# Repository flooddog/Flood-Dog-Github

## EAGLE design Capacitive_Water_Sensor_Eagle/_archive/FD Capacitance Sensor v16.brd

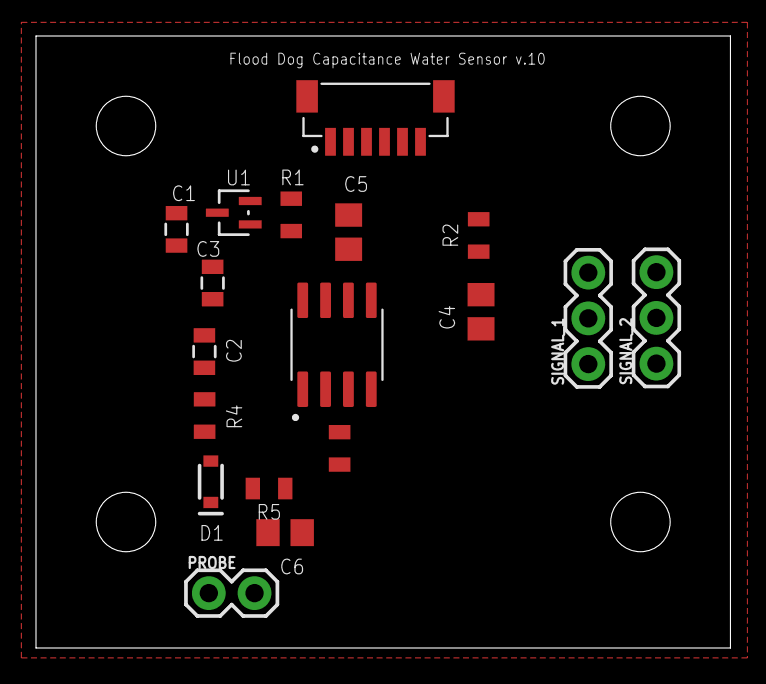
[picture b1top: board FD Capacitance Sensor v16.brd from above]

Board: 2 copper layers, 38.6 x 34.0 mm, 22 parts (0 on the bottom side), 12 nets, no tracks yet.

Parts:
C1: 0.1uF; 0805@1
C2: 1uF; 0805@1
C3: 10nF; 0805@1
C4: 10nf; C0805
C5: 470pf; C0805
C6: 1uF; C0805
D1: 250mA/100V; SOD-323
J1: BM06B-SRSS-TBT(LF)(SN); JST_BM06B-SRSS-TB(LF)(SN)
PROBE: 1X02
R1: 100k; 0805
R2: 1k; 0805
R3: 10k; 0805
R4: 330; 0805
R5: 1M; 0805
SIGNAL_1, SIGNAL_2: 1X03
U1: NTS4101PT1; SOT_101PT1_ONS
U2: TLC555CD; SOIC127P599X175-8N
U$1, U$2, U$3, U$4: STAND-OFF

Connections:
!EN: J1.3, R1.1, U1.1
+3V3: J1.2, R1.2, U1.2
GND: C1.2, C2.2, C3.2, C4.1, C5.1, C6.1, J1.1, J1.S1, J1.S2, PROBE.2, R5.1, SIGNAL_1.1, SIGNAL_2.1, U2.1
unnamed: C4.2, U2.5
unnamed: R3.1, U2.3
unnamed: C5.2, R2.1, U2.2, U2.6
unnamed: R2.2, R4.1, U2.7
PROBE+: D1.A, PROBE.1, R3.2
SIGNAL_A0: C6.2, D1.C, J1.4, R5.2
SIGNAL_A1: J1.5, SIGNAL_1.3
SIGNAL_A2: J1.6, SIGNAL_2.3
VCC: C1.1, C2.1, C3.1, R4.2, SIGNAL_1.2, SIGNAL_2.2, U1.3, U2.4, U2.8

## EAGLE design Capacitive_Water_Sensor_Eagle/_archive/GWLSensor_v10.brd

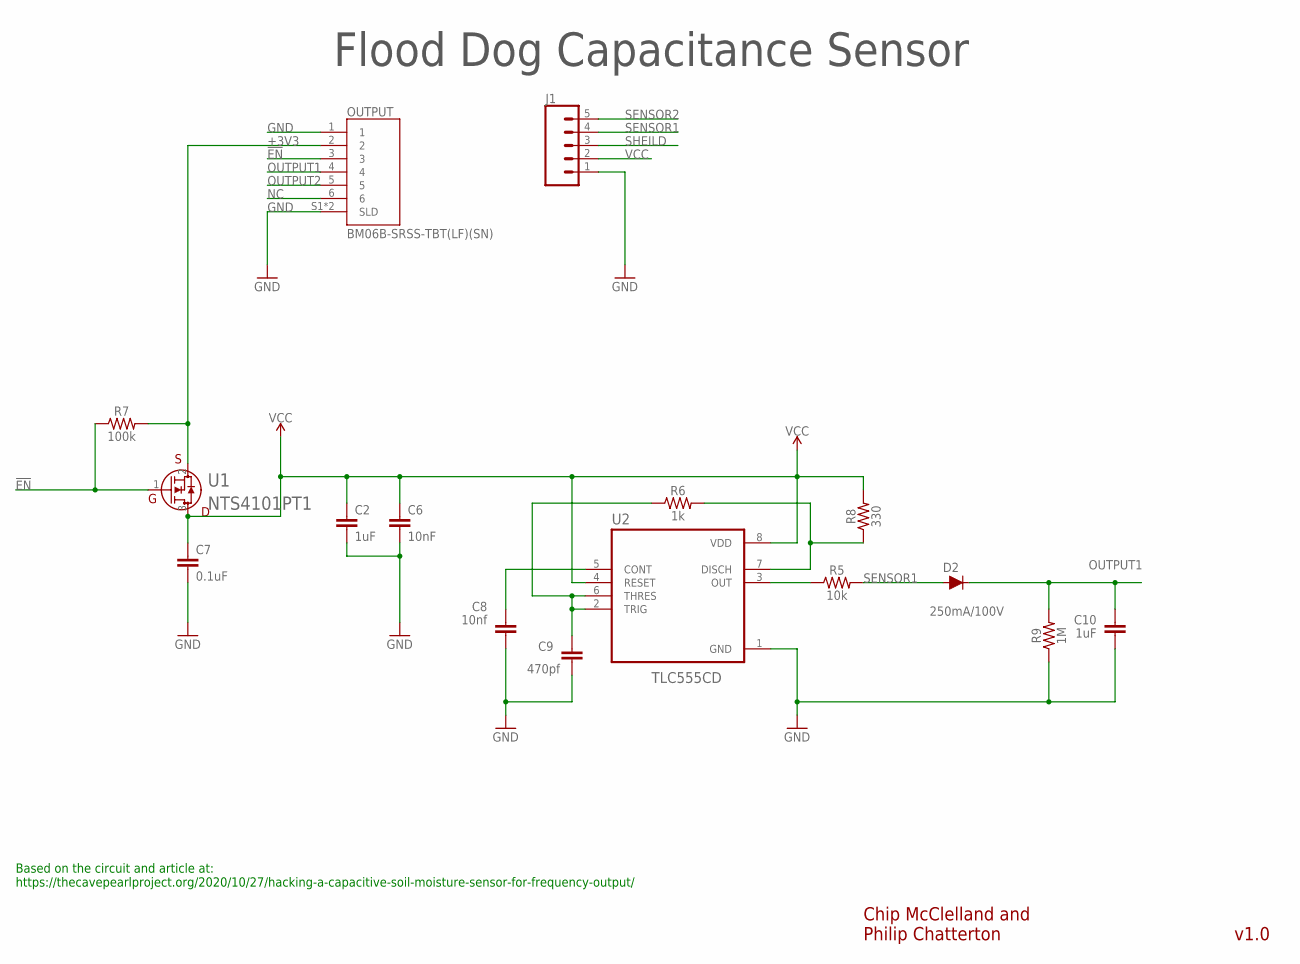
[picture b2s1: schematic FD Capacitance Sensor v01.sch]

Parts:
C2: 1uF; 0805@1
C6: 10nF; 0805@1
C7: 0.1uF; 0805@1
C8: 10nf; C0805
C9: 470pf; C0805
C10: 1uF; C0805
D2: 250mA/100V; SOD-323
J1: CONN_05SCREW; SCREWTERMINAL-3.5MM-5
OUTPUT: BM06B-SRSS-TBT(LF)(SN); JST_BM06B-SRSS-TB(LF)(SN)
R5: 10k; 0805
R6: 1k; 0805
R7: 100k; 0805; MPN MF-RES-0805-100K
R8: 330; 0805
R9: 1M; 0805
U1: NTS4101PT1; SOT_101PT1_ONS
U2: TLC555CD; SOIC127P599X175-8N

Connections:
!EN: OUTPUT.3, R7.1, U1.1 (G)
+3V3: OUTPUT.2, R7.2, U1.2 (S)
GND: C2.2, C6.2, C7.2, C8.1, C9.1, C10.1, J1.1, OUTPUT.1, OUTPUT.S1 (SLD), OUTPUT.S2 (SLD), R9.1, U2.1 (GND)
unnamed: C8.2, U2.5 (CONT)
unnamed: R5.1, U2.3 (OUT)
unnamed: C9.2, R6.1, U2.2 (TRIG), U2.6 (THRES)
unnamed: R6.2, R8.1, U2.7 (DISCH)
NC: OUTPUT.6
OUTPUT1: C10.2, D2.C, OUTPUT.4, R9.2
OUTPUT2: OUTPUT.5
SENSOR1: D2.A, J1.4, R5.2
SENSOR2: J1.5
SHEILD: J1.3
VCC: C2.1, C6.1, C7.1, J1.2, R8.2, U1.3 (D), U2.4 (RESET), U2.8 (VDD)

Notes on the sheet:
Flood Dog Capacitance Sensor
v1.0
Chip McClelland and Philip Chatterton
Based on the circuit and article at: https://thecavepearlproject.org/2020/10/27/hacking-a-capacitive-soil-moisture-sensor-for-frequency-output/

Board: 2 copper layers, 16 parts (0 on the bottom side), 10 nets, no tracks yet.

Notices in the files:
parts and their libraries:
SparkFun-Connectors: Licensing: Creative Commons ShareAlike 4.0 International - https://creativecommons.org/licenses/by-sa/4.0
